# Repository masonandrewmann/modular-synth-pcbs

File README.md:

A collection of PCBs I've designed since getting into DIY modular synths. Do not assume that any of these designs work or are good, many of them have errors I have not fixed yet. If you want to get some manufactured, go ahead but I'd urge you to contact me first and I can let you know any quirks of the board first! :~)

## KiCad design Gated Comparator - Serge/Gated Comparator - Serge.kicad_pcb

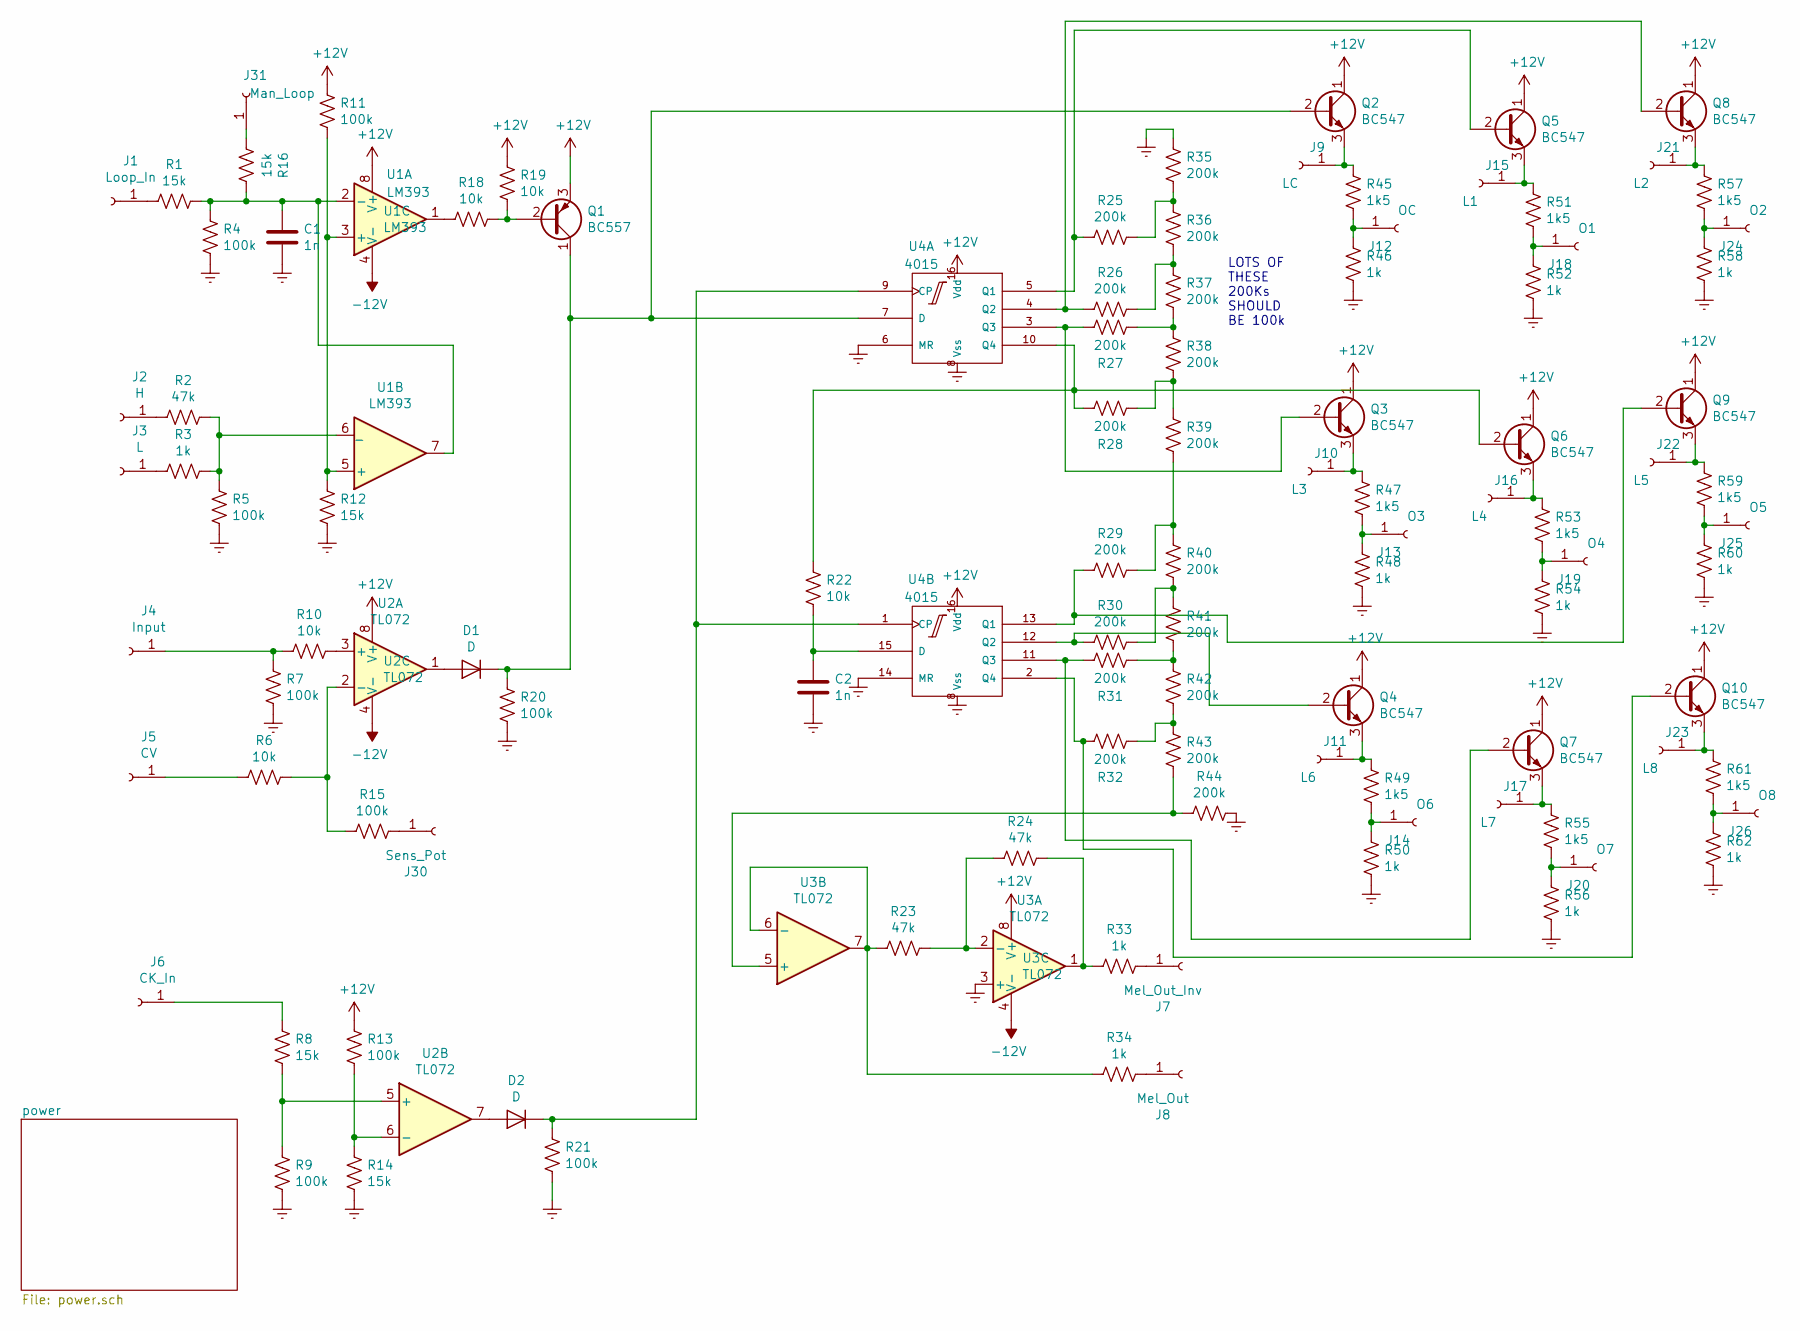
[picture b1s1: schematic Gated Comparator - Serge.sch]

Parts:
C1, C2: 1n; C_Rect_L7.0mm_W2.5mm_P5.00mm
D1, D2: D; D_T-1_P5.08mm_Horizontal
J1: Loop_In; SolderWirePad_1x01_Drill1mm
J2: H; SolderWirePad_1x01_Drill1mm
J3: L; SolderWirePad_1x01_Drill1mm
J4: Input; SolderWirePad_1x01_Drill1mm
J5: CV; SolderWirePad_1x01_Drill1mm
J6: CK_In; SolderWirePad_1x01_Drill1mm
J7: Mel_Out_Inv; SolderWirePad_1x01_Drill1mm
J8: Mel_Out; SolderWirePad_1x01_Drill1mm
J9: LC; SolderWirePad_1x01_Drill1mm
J10: L3; SolderWirePad_1x01_Drill1mm
J11: L6; SolderWirePad_1x01_Drill1mm
J12: OC; SolderWirePad_1x01_Drill1mm
J13: O3; SolderWirePad_1x01_Drill1mm
J14: O6; SolderWirePad_1x01_Drill1mm
J15: L1; SolderWirePad_1x01_Drill1mm
J16: L4; SolderWirePad_1x01_Drill1mm
J17: L7; SolderWirePad_1x01_Drill1mm
J18: O1; SolderWirePad_1x01_Drill1mm
J19: O4; SolderWirePad_1x01_Drill1mm
J20: O7; SolderWirePad_1x01_Drill1mm
J21: L2; SolderWirePad_1x01_Drill1mm
J22: L5; SolderWirePad_1x01_Drill1mm
J23: L8; SolderWirePad_1x01_Drill1mm
J24: O2; SolderWirePad_1x01_Drill1mm
J25: O5; SolderWirePad_1x01_Drill1mm
J26: O8; SolderWirePad_1x01_Drill1mm
J30: Sens_Pot; SolderWirePad_1x01_Drill1mm
J31: Man_Loop; SolderWirePad_1x01_Drill1mm
Q1: BC557; TO-92_Inline_Wide
Q2, Q3, Q4, Q5, Q6, Q7, Q8, Q9, Q10: BC547; TO-92_Inline_Wide
R1, R8, R12, R14, R16: 15k; R_Axial_DIN0207_L6.3mm_D2.5mm_P7.62mm_Horizontal
R2, R23, R24: 47k; R_Axial_DIN0207_L6.3mm_D2.5mm_P7.62mm_Horizontal
R3, R33, R34, R46, R48, R50, R52, R54, R56, R58, R60, R62: 1k; R_Axial_DIN0207_L6.3mm_D2.5mm_P7.62mm_Horizontal
R4, R5, R7, R9, R11, R13, R15, R20, R21: 100k; R_Axial_DIN0207_L6.3mm_D2.5mm_P7.62mm_Horizontal
R6, R10, R18, R19, R22: 10k; R_Axial_DIN0207_L6.3mm_D2.5mm_P7.62mm_Horizontal
R25, R26, R27, R28, R29, R30, R31, R32, R35, R36, R37, R38, R39, R40, R41, R42, R43, R44: 200k; R_Axial_DIN0207_L6.3mm_D2.5mm_P7.62mm_Horizontal
R45, R47, R49, R51, R53, R55, R57, R59, R61: 1k5; R_Axial_DIN0207_L6.3mm_D2.5mm_P7.62mm_Horizontal
U1: LM393; DIP-8_W7.62mm_Socket
U2, U3: TL072; DIP-8_W7.62mm_Socket
U4: 4015; DIP-16_W7.62mm_Socket

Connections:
+12V: Q1.3 (E), Q2.1 (C), Q3.1 (C), Q4.1 (C), Q5.1 (C), Q6.1 (C), Q7.1 (C), Q8.1 (C), Q9.1 (C), Q10.1 (C), R11.2, R13.1, R19.2, U1.8 (V+), U2.8 (V+), U3.8 (V+), U4.16 (Vdd); also elsewhere on the board
-12V: U1.4 (V-), U2.4 (V-), U3.4 (V-); also elsewhere on the board
Earth: C1.2, C2.2, R4.1, R5.1, R7.2, R9.2, R12.1, R14.2, R20.2, R21.2, R35.2, R44.2, R46.1, R48.1, R50.1, R52.1, R54.1, R56.1, R58.1, R60.1, R62.1, U3.3 (+), U4.6 (MR), U4.8 (Vss), U4.14 (MR); also elsewhere on the board
unnamed: C1.1, R1.1, R4.2, R16.1, U1.2 (-), U1.7
unnamed: C2.1, R22.2, U4.15 (D)
unnamed: D1.1 (K), Q1.1 (C), Q2.2 (B), R20.1, U4.7 (D)
unnamed: D1.2 (A), U2.1
unnamed: D2.1 (K), R21.1, U4.1 (CP), U4.9 (CP)
unnamed: D2.2 (A), U2.7
unnamed: J1.1, R1.2
unnamed: J2.1, R2.2
unnamed: J3.1, R3.2
unnamed: J4.1, R7.1, R10.1
unnamed: J5.1, R6.1
unnamed: J6.1, R8.1
unnamed: J7.1, R33.2
unnamed: J8.1, R34.2
unnamed: J9.1, Q2.3 (E), R45.2
unnamed: J10.1, Q3.3 (E), R47.2
unnamed: J11.1, Q4.3 (E), R49.2
unnamed: J12.1, R45.1, R46.2
unnamed: J13.1, R47.1, R48.2
unnamed: J14.1, R49.1, R50.2
unnamed: J15.1, Q5.3 (E), R51.2
unnamed: J16.1, Q6.3 (E), R53.2
unnamed: J17.1, Q7.3 (E), R55.2
unnamed: J18.1, R51.1, R52.2
unnamed: J19.1, R53.1, R54.2
unnamed: J20.1, R55.1, R56.2
unnamed: J21.1, Q8.3 (E), R57.2
unnamed: J22.1, Q9.3 (E), R59.2
unnamed: J23.1, Q10.3 (E), R61.2
unnamed: J24.1, R57.1, R58.2
unnamed: J25.1, R59.1, R60.2
unnamed: J26.1, R61.1, R62.2
unnamed: J30.1, R15.2
unnamed: J31.1, R16.2
unnamed: Q1.2 (B), R18.1, R19.1
unnamed: Q3.2 (B), R27.2, U4.3 (Q3)
unnamed: Q4.2 (B), R30.2, U4.12 (Q2)
unnamed: Q5.2 (B), R25.2, U4.5 (Q1)
unnamed: Q6.2 (B), R22.1, R28.2, U4.10 (Q4)
unnamed: Q7.2 (B), R31.2, U4.11 (Q3)
unnamed: Q8.2 (B), R26.2, U4.4 (Q2)
unnamed: Q9.2 (B), R29.2, U4.13 (Q1)
unnamed: Q10.2 (B), R32.2, U4.2 (Q4)
unnamed: R2.1, R3.1, R5.2, U1.6 (_)
unnamed: R8.2, R9.1, U2.5 (+)
unnamed: R10.2, U2.3 (+)
unnamed: R11.1, R12.2, U1.3 (+), U1.5 (+)
unnamed: R13.2, R14.1, U2.6 (-)
unnamed: R6.2, R15.1, U2.2 (-)
unnamed: R18.2, U1.1
unnamed: R23.1, R34.1, U3.6 (-), U3.7
unnamed: R23.2, R24.1, U3.2 (-)
unnamed: R24.2, R33.1, U3.1
unnamed: R25.1, R35.1, R36.2
unnamed: R26.1, R36.1, R37.2
unnamed: R27.1, R37.1, R38.2
unnamed: R28.1, R38.1, R39.2
unnamed: R29.1, R39.1, R40.2
unnamed: R30.1, R40.1, R41.2
unnamed: R31.1, R41.1, R42.2
unnamed: R32.1, R42.1, R43.2
unnamed: R43.1, R44.1, U3.5 (+)

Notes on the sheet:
LOTS OF THESE 200Ks SHOULD BE 100k

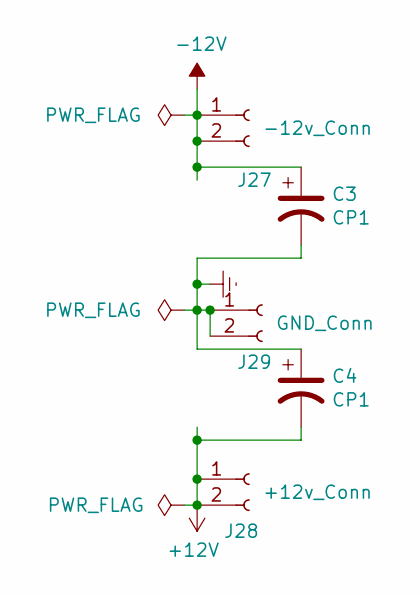
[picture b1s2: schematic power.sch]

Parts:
C3, C4: CP1; CP_Radial_D5.0mm_P2.0mm_Bigger_Holes
J27: -12v_Conn; SolderWirePad_1x02_P3.81mm_Drill1mm
J28: +12v_Conn; SolderWirePad_1x02_P3.81mm_Drill1mm
J29: GND_Conn; SolderWirePad_1x02_P3.81mm_Drill1mm

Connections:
+12V: C4.2, J28.1, J28.2; also elsewhere on the board
-12V: C3.1, J27.1, J27.2; also elsewhere on the board
Earth: C3.2, C4.1, J29.1, J29.2; also elsewhere on the board

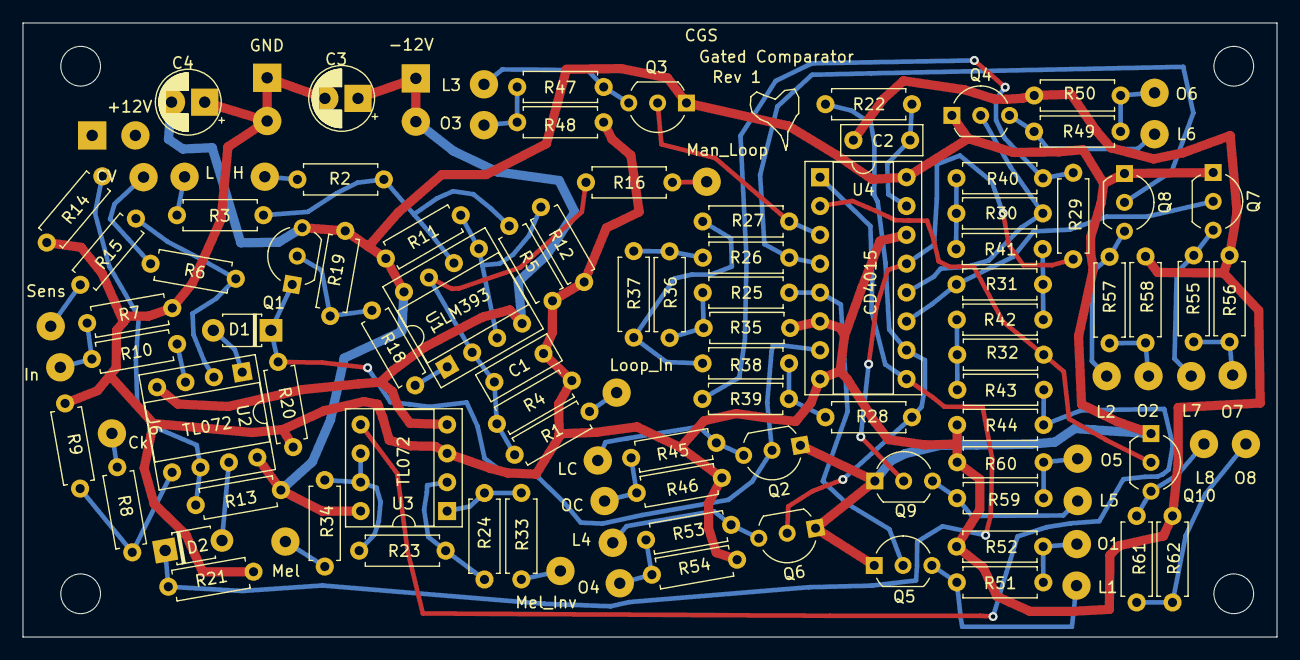
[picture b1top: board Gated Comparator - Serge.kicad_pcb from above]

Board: 2 copper layers, 110.5 x 54.1 mm, 112 parts (0 on the bottom side), 65 nets.

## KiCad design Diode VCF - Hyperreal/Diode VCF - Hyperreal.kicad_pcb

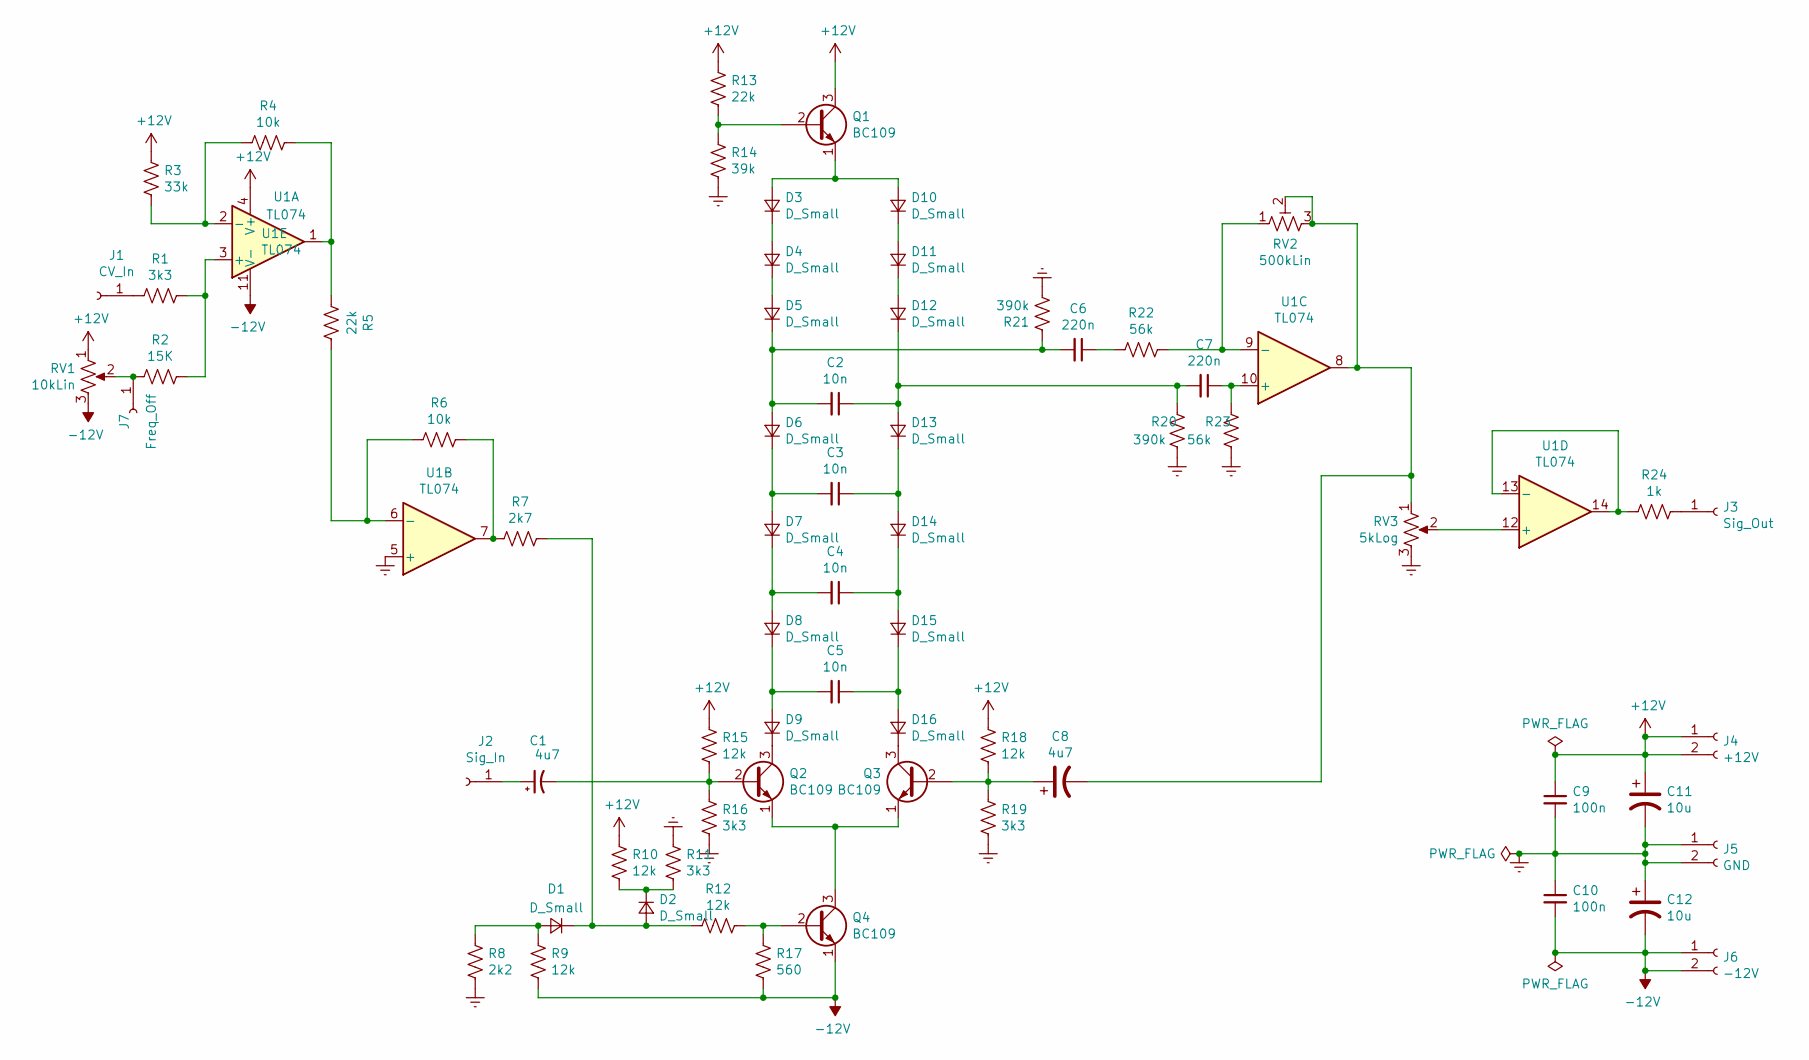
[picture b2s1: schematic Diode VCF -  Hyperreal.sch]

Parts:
C1, C8: 4u7; CP_Radial_D5.0mm_P2.0mm_Bigger_Holes
C2, C3, C4, C5: 10n; C_Rect_L7.0mm_W2.5mm_P5.00mm
C6, C7: 220n; C_Rect_L7.0mm_W2.5mm_P5.00mm
C9, C10: 100n; C_Rect_L7.0mm_W2.5mm_P5.00mm
C11, C12: 10u; CP_Radial_D5.0mm_P2.0mm_Bigger_Holes
D1, D2, D3, D4, D5, D6, D7, D8, D9, D10, D11, D12, D13, D14, D15, D16: D_Small; D_T-1_P5.08mm_Horizontal
J1: CV_In; SolderWirePad_1x01_Drill1mm
J2: Sig_In; SolderWirePad_1x01_Drill1mm
J3: Sig_Out; SolderWirePad_1x01_Drill1mm
J4: +12V; SolderWirePad_1x02_P3.81mm_Drill1mm
J5: GND; SolderWirePad_1x02_P3.81mm_Drill1mm
J6: -12V; SolderWirePad_1x02_P3.81mm_Drill1mm
J7: Freq_Off; SolderWirePad_1x01_Drill1mm
Q1, Q2, Q3, Q4: BC109; TO-18-3
R1, R11, R16, R19: 3k3; R_Axial_DIN0207_L6.3mm_D2.5mm_P7.62mm_Horizontal
R2: 15K; R_Axial_DIN0207_L6.3mm_D2.5mm_P7.62mm_Horizontal
R3: 33k; R_Axial_DIN0207_L6.3mm_D2.5mm_P7.62mm_Horizontal
R4, R6: 10k; R_Axial_DIN0207_L6.3mm_D2.5mm_P7.62mm_Horizontal
R5, R13: 22k; R_Axial_DIN0207_L6.3mm_D2.5mm_P7.62mm_Horizontal
R7: 2k7; R_Axial_DIN0207_L6.3mm_D2.5mm_P7.62mm_Horizontal
R8: 2k2; R_Axial_DIN0207_L6.3mm_D2.5mm_P7.62mm_Horizontal
R9, R10, R12, R15, R18: 12k; R_Axial_DIN0207_L6.3mm_D2.5mm_P7.62mm_Horizontal
R14: 39k; R_Axial_DIN0207_L6.3mm_D2.5mm_P7.62mm_Horizontal
R17: 560; R_Axial_DIN0207_L6.3mm_D2.5mm_P7.62mm_Horizontal
R20, R21: 390k; R_Axial_DIN0207_L6.3mm_D2.5mm_P7.62mm_Horizontal
R22, R23: 56k; R_Axial_DIN0207_L6.3mm_D2.5mm_P7.62mm_Horizontal
R24: 1k; R_Axial_DIN0207_L6.3mm_D2.5mm_P7.62mm_Horizontal
RV1: 10kLin
RV2: 500kLin; Potentiometer_Runtron_RM-065_Vertical
RV3: 5kLog
U1: TL074; DIP-14_W7.62mm_Socket

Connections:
+12V: C9.1, C11.1, J4.1, J4.2, Q1.3 (C), R3.1, R10.2, R13.2, R15.2, R18.2, RV1.1, U1.4 (V+); also elsewhere on the board
-12V: C10.2, C12.2, J6.1, J6.2, Q4.1 (E), R9.1, R17.2, RV1.3, U1.11 (V-); also elsewhere on the board
Earth: C9.2, C10.1, C11.2, C12.1, J5.1, J5.2, R8.1, R11.2, R14.1, R16.1, R19.1, R20.2, R21.1, R23.2, RV3.3, U1.5 (+)
unnamed: C1.1, J2.1
unnamed: C1.2, Q2.2 (B), R15.1, R16.2
unnamed: C2.1, C7.2, D12.1 (K), D13.2 (A), R20.1
unnamed: C2.2, C6.2, D5.1 (K), D6.2 (A), R21.2
unnamed: C3.1, D13.1 (K), D14.2 (A)
unnamed: C3.2, D6.1 (K), D7.2 (A)
unnamed: C4.1, D14.1 (K), D15.2 (A)
unnamed: C4.2, D7.1 (K), D8.2 (A)
unnamed: C5.1, D15.1 (K), D16.2 (A)
unnamed: C5.2, D8.1 (K), D9.2 (A)
unnamed: C6.1, R22.2
unnamed: C7.1, R23.1, U1.10 (+)
unnamed: C8.1, Q3.2 (B), R18.1, R19.2
unnamed: C8.2, RV2.2, RV2.3, RV3.1, U1.8
unnamed: D1.1 (K), D2.2 (A), R7.1, R12.2
unnamed: D1.2 (A), R8.2, R9.2
unnamed: D2.1 (K), R10.1, R11.1
unnamed: D3.1 (K), D4.2 (A)
unnamed: D4.1 (K), D5.2 (A)
unnamed: D9.1 (K), Q2.3 (C)
unnamed: D10.1 (K), D11.2 (A)
unnamed: D3.2 (A), D10.2 (A), Q1.1 (E)
unnamed: D11.1 (K), D12.2 (A)
unnamed: D16.1 (K), Q3.3 (C)
unnamed: J1.1, R1.2
unnamed: J3.1, R24.1
unnamed: J7.1, R2.2, RV1.2
unnamed: Q1.2 (B), R13.1, R14.2
unnamed: Q2.1 (E), Q3.1 (E), Q4.3 (C)
unnamed: Q4.2 (B), R12.1, R17.1
unnamed: R1.1, R2.1, U1.3 (+)
unnamed: R3.2, R4.2, U1.2 (-)
unnamed: R4.1, R5.2, U1.1
unnamed: R5.1, R6.2, U1.6 (-)
unnamed: R6.1, R7.2, U1.7
unnamed: R22.1, RV2.1, U1.9 (-)
unnamed: R24.2, U1.13 (-), U1.14
unnamed: RV3.2, U1.12 (+)

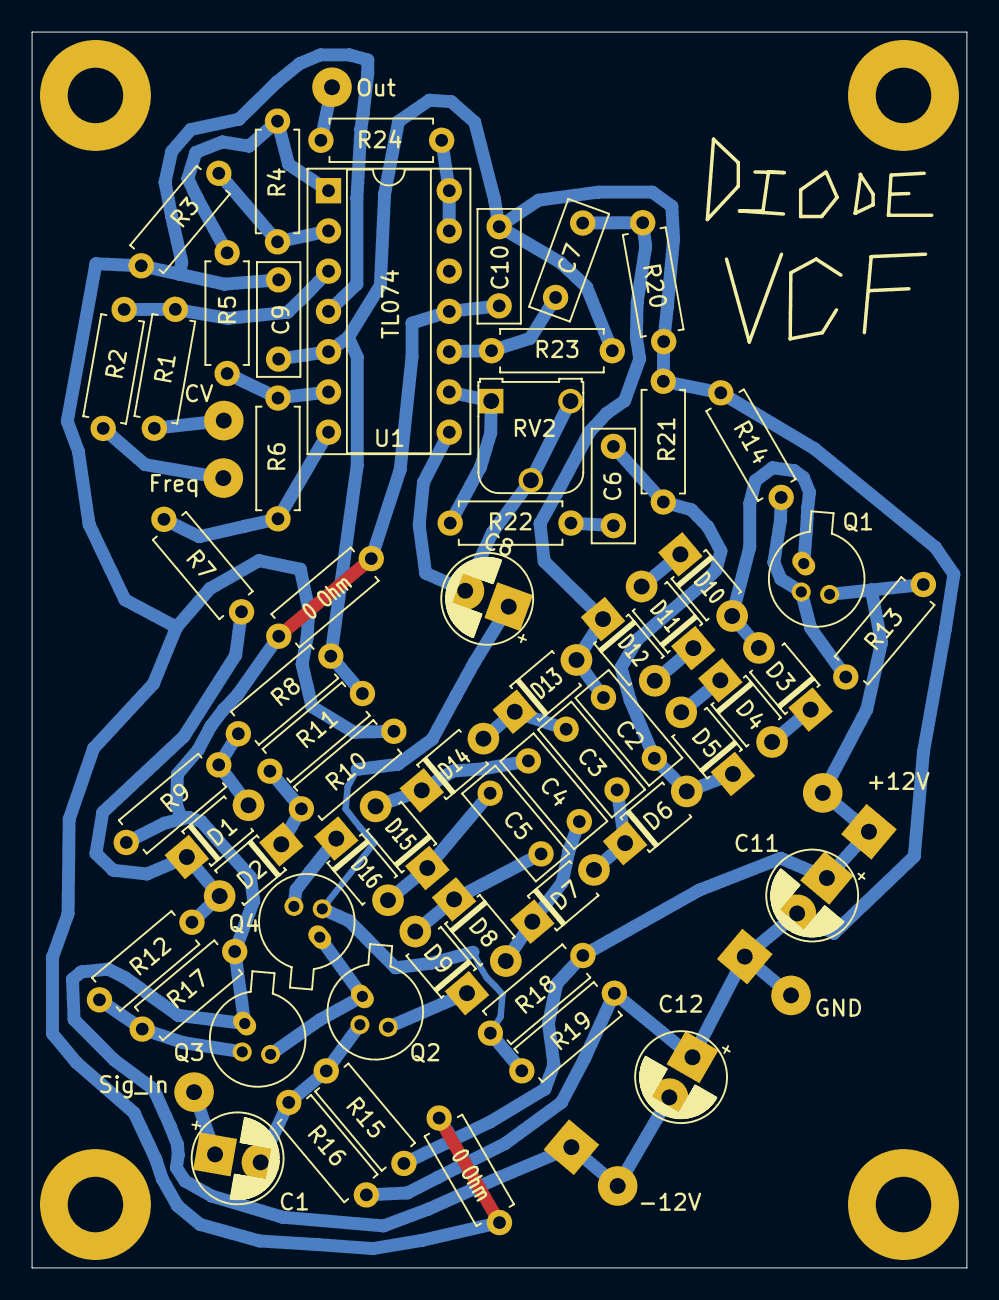
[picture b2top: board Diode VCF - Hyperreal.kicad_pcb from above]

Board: 2 copper layers, 59.0 x 78.0 mm, 67 parts (0 on the bottom side), 40 nets.

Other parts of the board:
0 Ohm, 0 Ohm#2: R_Axial_DIN0207_L6.3mm_D2.5mm_P7.62mm_Horizontal

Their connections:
+12V: 0 Ohm#2.1, 0 Ohm#2.2; also elsewhere on the board
-12V: 0 Ohm.1, 0 Ohm.2; also elsewhere on the board

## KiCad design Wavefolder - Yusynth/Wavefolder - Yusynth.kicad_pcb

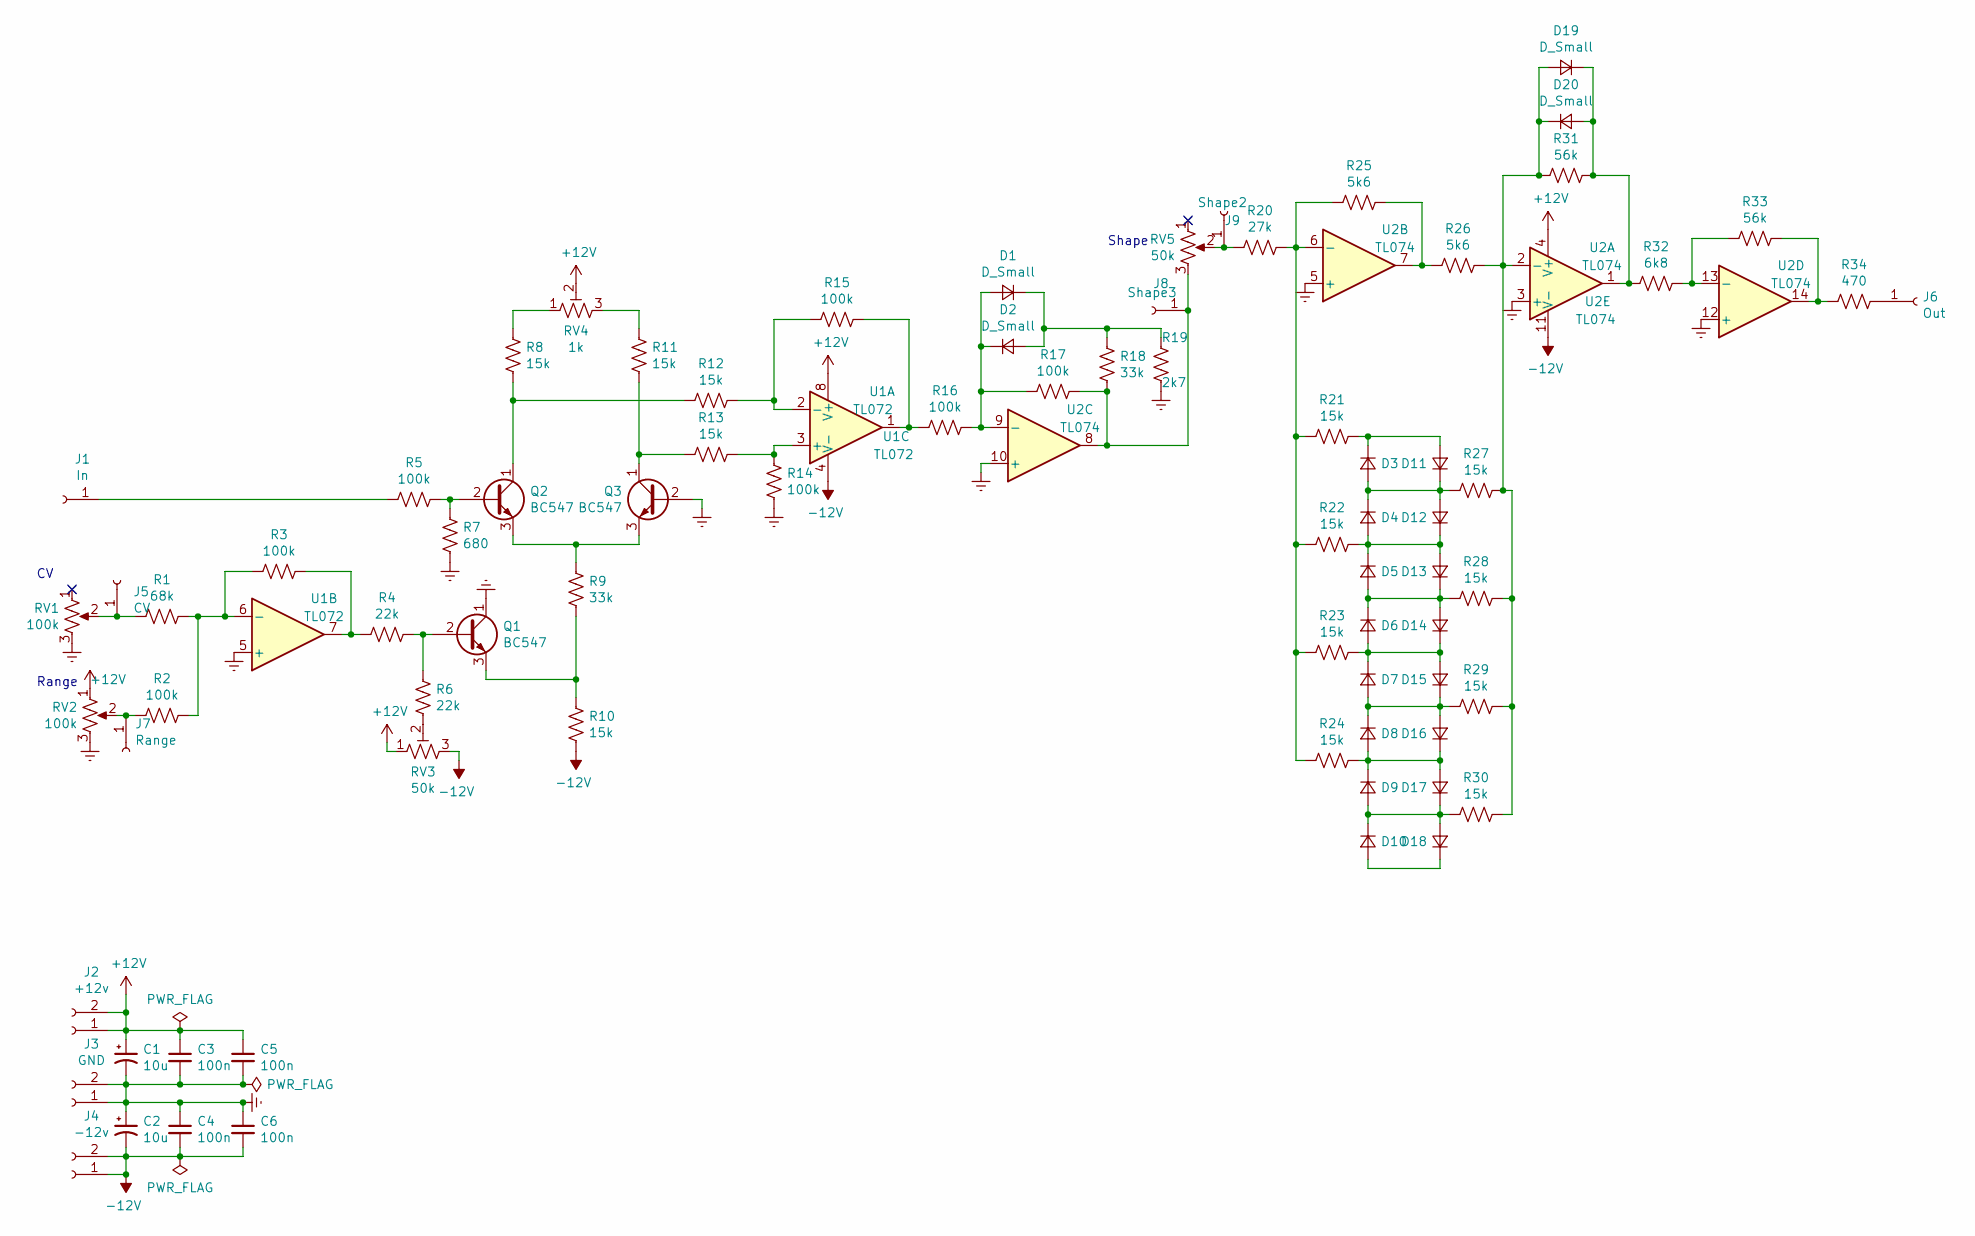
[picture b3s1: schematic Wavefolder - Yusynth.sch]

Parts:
C1, C2: 10u; CP_Radial_D5.0mm_P2.50mm
C3, C4, C5, C6: 100n; C_Rect_L7.0mm_W2.5mm_P5.00mm
D1, D2, D3, D4, D5, D6, D7, D8, D9, D10, D11, D12, D13, D14, D15, D16, D17, D18, D19, D20: D_Small; D_T-1_P5.08mm_Horizontal
J1: In; SolderWirePad_1x01_Drill1mm
J2: +12v; SolderWirePad_1x02_P3.81mm_Drill1mm
J3: GND; SolderWirePad_1x02_P3.81mm_Drill1mm
J4: -12v; SolderWirePad_1x02_P3.81mm_Drill1mm
J5: CV; SolderWirePad_1x01_Drill1mm
J6: Out; SolderWirePad_1x01_Drill1mm
J7: Range; SolderWirePad_1x01_Drill1mm
J8: Shape3; SolderWirePad_1x01_Drill1mm
J9: Shape2; SolderWirePad_1x01_Drill1mm
Q1, Q2, Q3: BC547; TO-92_Inline_Wide
R1: 68k; R_Axial_DIN0207_L6.3mm_D2.5mm_P7.62mm_Horizontal
R2, R3, R5, R14, R15, R16, R17: 100k; R_Axial_DIN0207_L6.3mm_D2.5mm_P7.62mm_Horizontal
R4, R6: 22k; R_Axial_DIN0207_L6.3mm_D2.5mm_P7.62mm_Horizontal
R7: 680; R_Axial_DIN0207_L6.3mm_D2.5mm_P7.62mm_Horizontal
R8, R10, R11, R12, R13, R21, R22, R23, R24, R27, R28, R29, R30: 15k; R_Axial_DIN0207_L6.3mm_D2.5mm_P7.62mm_Horizontal
R9, R18: 33k; R_Axial_DIN0207_L6.3mm_D2.5mm_P7.62mm_Horizontal
R19: 2k7; R_Axial_DIN0207_L6.3mm_D2.5mm_P7.62mm_Horizontal
R20: 27k; R_Axial_DIN0207_L6.3mm_D2.5mm_P7.62mm_Horizontal
R25, R26: 5k6; R_Axial_DIN0207_L6.3mm_D2.5mm_P7.62mm_Horizontal
R31, R33: 56k; R_Axial_DIN0207_L6.3mm_D2.5mm_P7.62mm_Horizontal
R32: 6k8; R_Axial_DIN0207_L6.3mm_D2.5mm_P7.62mm_Horizontal
R34: 470; R_Axial_DIN0207_L6.3mm_D2.5mm_P7.62mm_Horizontal
RV1, RV2: 100k
RV3: 50k; Potentiometer_Runtron_RM-065_Vertical
RV4: 1k; Potentiometer_Runtron_RM-065_Vertical
RV5: 50k
U1: TL072; DIP-8_W7.62mm_Socket
U2: TL074; DIP-14_W7.62mm_Socket

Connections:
+12V: C1.1, C3.1, C5.1, J2.1, J2.2, RV2.1, RV3.1, RV4.2, U1.8 (V+), U2.4 (V+)
-12V: C2.2, C4.2, C6.2, J4.1, J4.2, R10.1, RV3.3, U1.4 (V-), U2.11 (V-)
Earth: C1.2, C2.1, C3.2, C4.1, C5.2, C6.1, J3.1, J3.2, Q1.1 (C), Q3.2 (B), R7.1, R14.2, R19.1, RV1.3, RV2.3, U1.5 (+), U2.3 (+), U2.5 (+), U2.10 (+), U2.12 (+)
unnamed: D1.1 (K), D2.2 (A), R18.2, R19.2
unnamed: D1.2 (A), D2.1 (K), R16.1, R17.2, U2.9 (-)
unnamed: D9.2 (A), D10.1 (K), D17.1 (K), D18.2 (A), R30.1
unnamed: D10.2 (A), D18.1 (K)
unnamed: D3.2 (A), D4.1 (K), D11.1 (K), D12.2 (A), R27.1
unnamed: D3.1 (K), D11.2 (A), R21.2
unnamed: D4.2 (A), D5.1 (K), D12.1 (K), D13.2 (A), R22.2
unnamed: D5.2 (A), D6.1 (K), D13.1 (K), D14.2 (A), R28.1
unnamed: D6.2 (A), D7.1 (K), D14.1 (K), D15.2 (A), R23.2
unnamed: D7.2 (A), D8.1 (K), D15.1 (K), D16.2 (A), R29.1
unnamed: D8.2 (A), D9.1 (K), D16.1 (K), D17.2 (A), R24.2
unnamed: D19.1 (K), D20.2 (A), R31.2, R32.1, U2.1
unnamed: D19.2 (A), D20.1 (K), R26.2, R27.2, R28.2, R29.2, R30.2, R31.1, U2.2 (-)
unnamed: J1.1, R5.1
unnamed: J5.1, R1.2, RV1.2
unnamed: J6.1, R34.2
unnamed: J7.1, R2.2, RV2.2
unnamed: J8.1, R17.1, R18.1, RV5.3, U2.8
unnamed: J9.1, R20.1, RV5.2
unnamed: Q1.2 (B), R4.1, R6.2
unnamed: Q1.3 (E), R9.1, R10.2
unnamed: Q2.1 (C), R8.1, R12.1
unnamed: Q2.2 (B), R5.2, R7.2
unnamed: Q2.3 (E), Q3.3 (E), R9.2
unnamed: Q3.1 (C), R11.1, R13.1
unnamed: R1.1, R2.1, R3.2, U1.6 (-)
unnamed: R3.1, R4.2, U1.7
unnamed: R6.1, RV3.2
unnamed: R8.2, RV4.1
unnamed: R11.2, RV4.3
unnamed: R12.2, R15.2, U1.2 (-)
unnamed: R13.2, R14.1, U1.3 (+)
unnamed: R15.1, R16.2, U1.1
unnamed: R20.2, R21.1, R22.1, R23.1, R24.1, R25.1, U2.6 (-)
unnamed: R25.2, R26.1, U2.7
unnamed: R32.2, R33.1, U2.13 (-)
unnamed: R33.2, R34.1, U2.14

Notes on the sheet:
Range
Shape

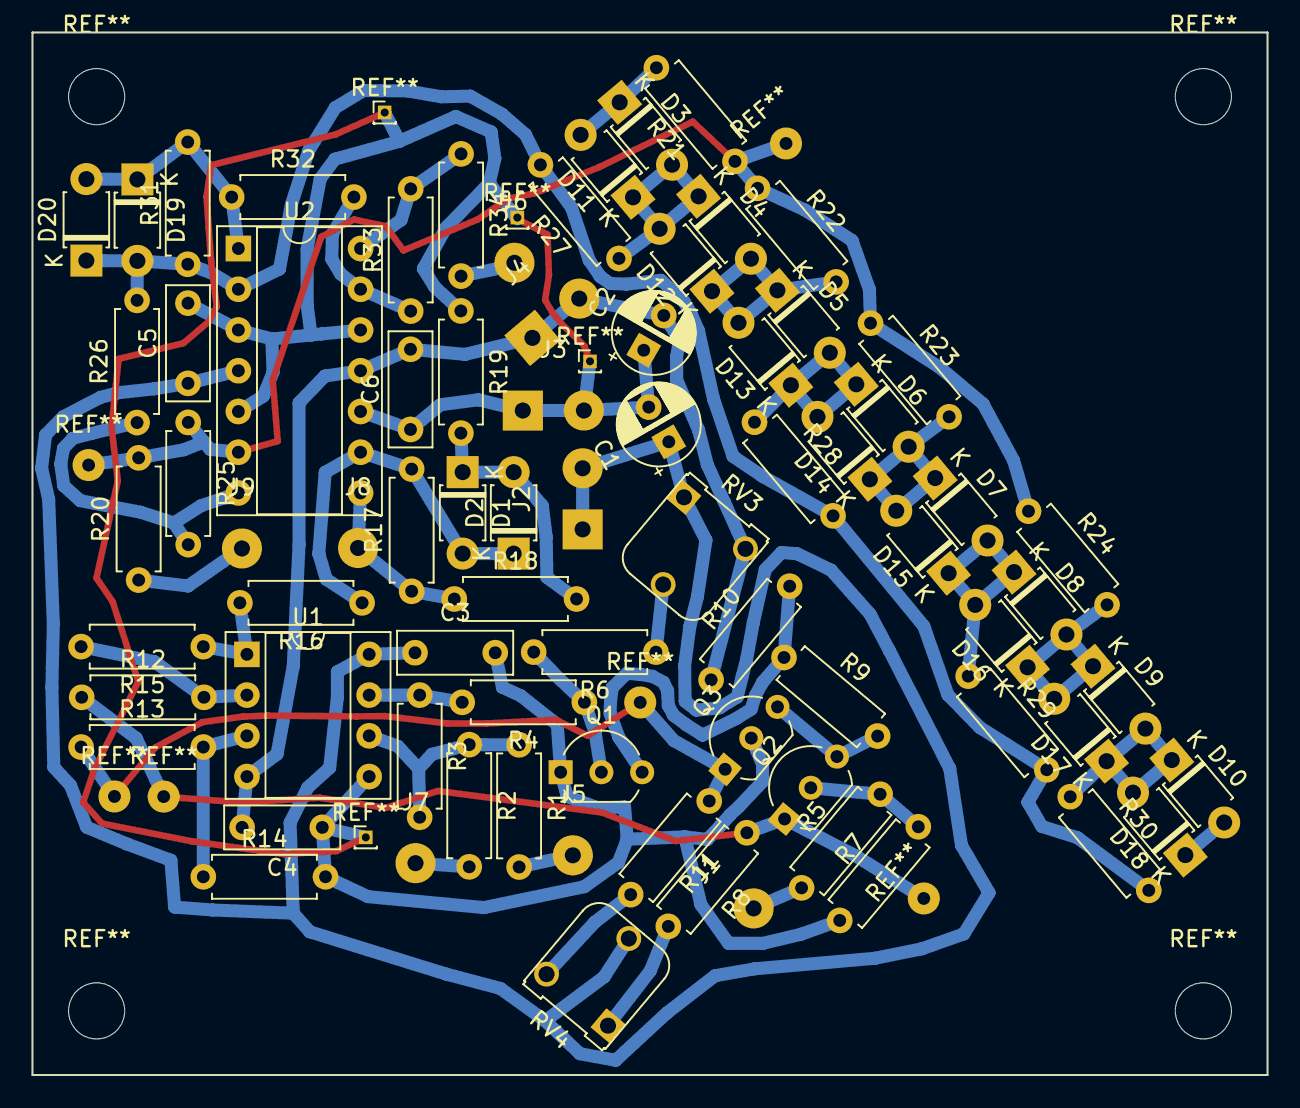
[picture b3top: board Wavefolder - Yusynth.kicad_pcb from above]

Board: 2 copper layers, 77.0 x 65.0 mm, 76 parts (0 on the bottom side), 40 nets.

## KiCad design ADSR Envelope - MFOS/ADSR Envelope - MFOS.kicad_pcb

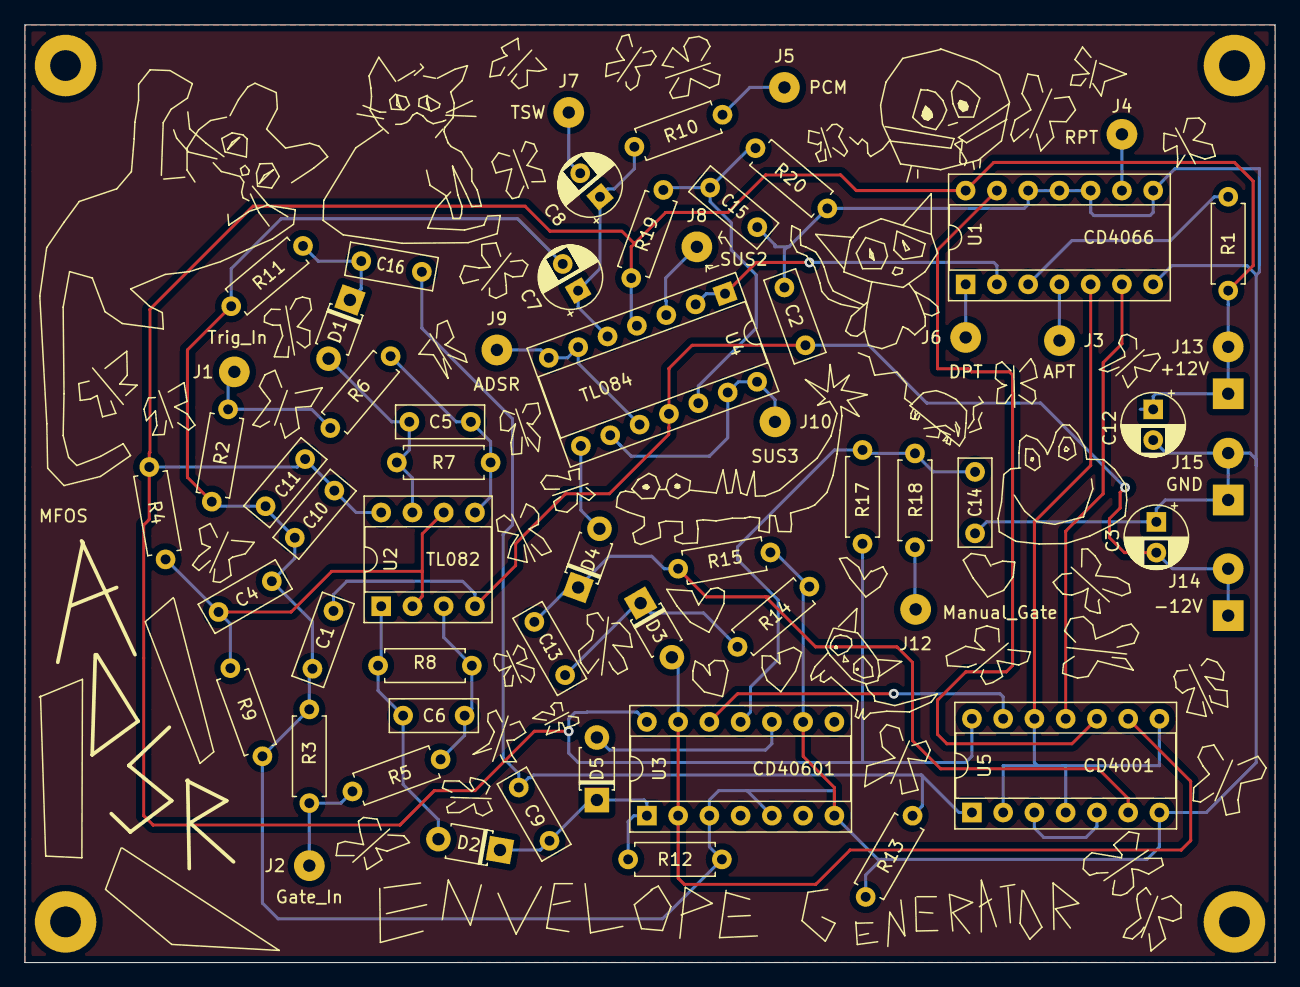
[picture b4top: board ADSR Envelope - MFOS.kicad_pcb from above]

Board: 2 copper layers, 101.6 x 76.2 mm, 59 parts (0 on the bottom side), 37 nets.

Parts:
C1, C2, C4, C10, C11, C14, C15: 0.1uF; C_Rect_L7.0mm_W2.5mm_P5.00mm
C3, C12: 10uF; CP_Radial_D5.0mm_P2.50mm
C5, C6: 100pF; C_Rect_L7.0mm_W2.5mm_P5.00mm
C7: 1uF; CP_Radial_D5.0mm_P2.50mm
C8: 15uF; CP_Radial_D5.0mm_P2.50mm
C9, C13: 0.001uF; C_Rect_L7.0mm_W2.5mm_P5.00mm
C16: 0.01uF; C_Rect_L7.0mm_W2.5mm_P5.00mm
D1, D2, D3, D4, D5: D; D_T-1_P5.08mm_Horizontal
J1: Trig_In; SolderWirePad_1x01_Drill1mm
J2: Gate_In; SolderWirePad_1x01_Drill1mm
J3: APT; SolderWirePad_1x01_Drill1mm
J4: RPT; SolderWirePad_1x01_Drill1mm
J5: PCM; SolderWirePad_1x01_Drill1mm
J6: DPT; SolderWirePad_1x01_Drill1mm
J7: TSW; SolderWirePad_1x01_Drill1mm
J8: SUS2; SolderWirePad_1x01_Drill1mm
J9: ADSR; SolderWirePad_1x01_Drill1mm
J10: SUS3; SolderWirePad_1x01_Drill1mm
J12: Manual_Gate; SolderWirePad_1x01_Drill1mm
J13: +12V_Conn; SolderWirePad_1x02_P3.81mm_Drill1mm
J14: -12V_Conn; SolderWirePad_1x02_P3.81mm_Drill1mm
J15: GND_Conn; SolderWirePad_1x02_P3.81mm_Drill1mm
R1, R10: 1K; R_Axial_DIN0207_L6.3mm_D2.5mm_P7.62mm_Horizontal
R2, R3, R11, R12, R14, R18, R20: 10K; R_Axial_DIN0207_L6.3mm_D2.5mm_P7.62mm_Horizontal
R4, R13, R15: 100K; R_Axial_DIN0207_L6.3mm_D2.5mm_P7.62mm_Horizontal
R5, R6, R9: 20K; R_Axial_DIN0207_L6.3mm_D2.5mm_P7.62mm_Horizontal
R7, R8: 1M; R_Axial_DIN0207_L6.3mm_D2.5mm_P7.62mm_Horizontal
R17: 47K; R_Axial_DIN0207_L6.3mm_D2.5mm_P7.62mm_Horizontal
R19: 2K; R_Axial_DIN0207_L6.3mm_D2.5mm_P7.62mm_Horizontal
U1: 4066; DIP-14_W7.62mm_Socket
U2: TL082; DIP-8_W7.62mm_Socket
U3: CD40106; DIP-14_W7.62mm_Socket
U4: TL084; DIP-14_W7.62mm_Socket
U5: 4001; DIP-14_W7.62mm_Socket

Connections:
+12V: C10.1, C11.1, C12.1, J13.1, J13.2, R1.1, R4.2, R17.1, R19.1, U1.14, U2.8, U3.14, U4.4, U5.14
-12V: C1.2, C2.2, C3.2, J14.1, J14.2, U2.4, U4.11
A: U1.5, U5.2, U5.4, U5.8, U5.12
D: U1.13, U5.10
Earth: C1.1, C2.1, C3.1, C4.1, C7.2, C10.2, C11.2, C12.2, C14.2, C15.2, J15.1, J15.2, R2.2, R3.2, R9.1, R11.1, R12.2, R13.1, R14.2, R15.2, R20.2, U1.7, U1.8, U1.10, U1.11, U1.12, U3.3, U3.5, U3.7, U3.9, U5.7
unnamed: C4.2, R4.1, R9.2, U2.2, U2.6
unnamed: C5.1, D1.2, R7.1, U2.7
unnamed: C5.2, R6.1, R7.2, U2.5
unnamed: C6.1, D2.2, R8.1, U2.1
unnamed: C6.2, R5.1, R8.2, U2.3
unnamed: C7.1, C8.1, R10.1, U4.5
unnamed: C8.2, J7.1
unnamed: C9.2, D2.1, D5.1, R12.1, U3.1
unnamed: C13.1, D4.1, R15.1, U5.6
unnamed: C13.2, D3.1, R14.1
unnamed: C14.1, R17.2, R18.2, U3.11
unnamed: C15.1, R19.2, R20.1, U4.12
unnamed: C9.1, C16.1, R13.2, U5.1
unnamed: C16.2, D1.1, R11.2
unnamed: D3.2, U3.2, U3.13, U5.9
unnamed: D4.2, U4.8
unnamed: D5.2, U3.10
unnamed: J1.1, R2.1, R6.2
unnamed: J2.1, R3.1, R5.2
unnamed: J3.1, U1.4
unnamed: J4.1, U1.9
unnamed: J5.1, R10.2
unnamed: J6.1, U1.1
unnamed: J8.1, U4.3
unnamed: J9.1, U4.6, U4.7, U4.10
unnamed: J10.1, U4.9, U4.13, U4.14
unnamed: J12.1, R18.1
unnamed: R1.2, U1.3
unnamed: U1.2, U4.1, U4.2
unnamed: U3.12, U5.13
unnamed: U5.3, U5.5
R: U1.6, U5.11
